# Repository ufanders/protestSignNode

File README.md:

# protestSignNode
This is a local driver for each of the protestSign display modules. It uses simplex RS-485 as the link back to the BeagleBone Black host and performs display refresh.

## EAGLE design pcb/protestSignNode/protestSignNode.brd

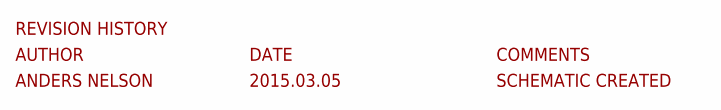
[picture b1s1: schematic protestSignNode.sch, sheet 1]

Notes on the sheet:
REVISION HISTORY
AUTHOR
DATE
COMMENTS
ANDERS NELSON
2015.03.05
SCHEMATIC CREATED

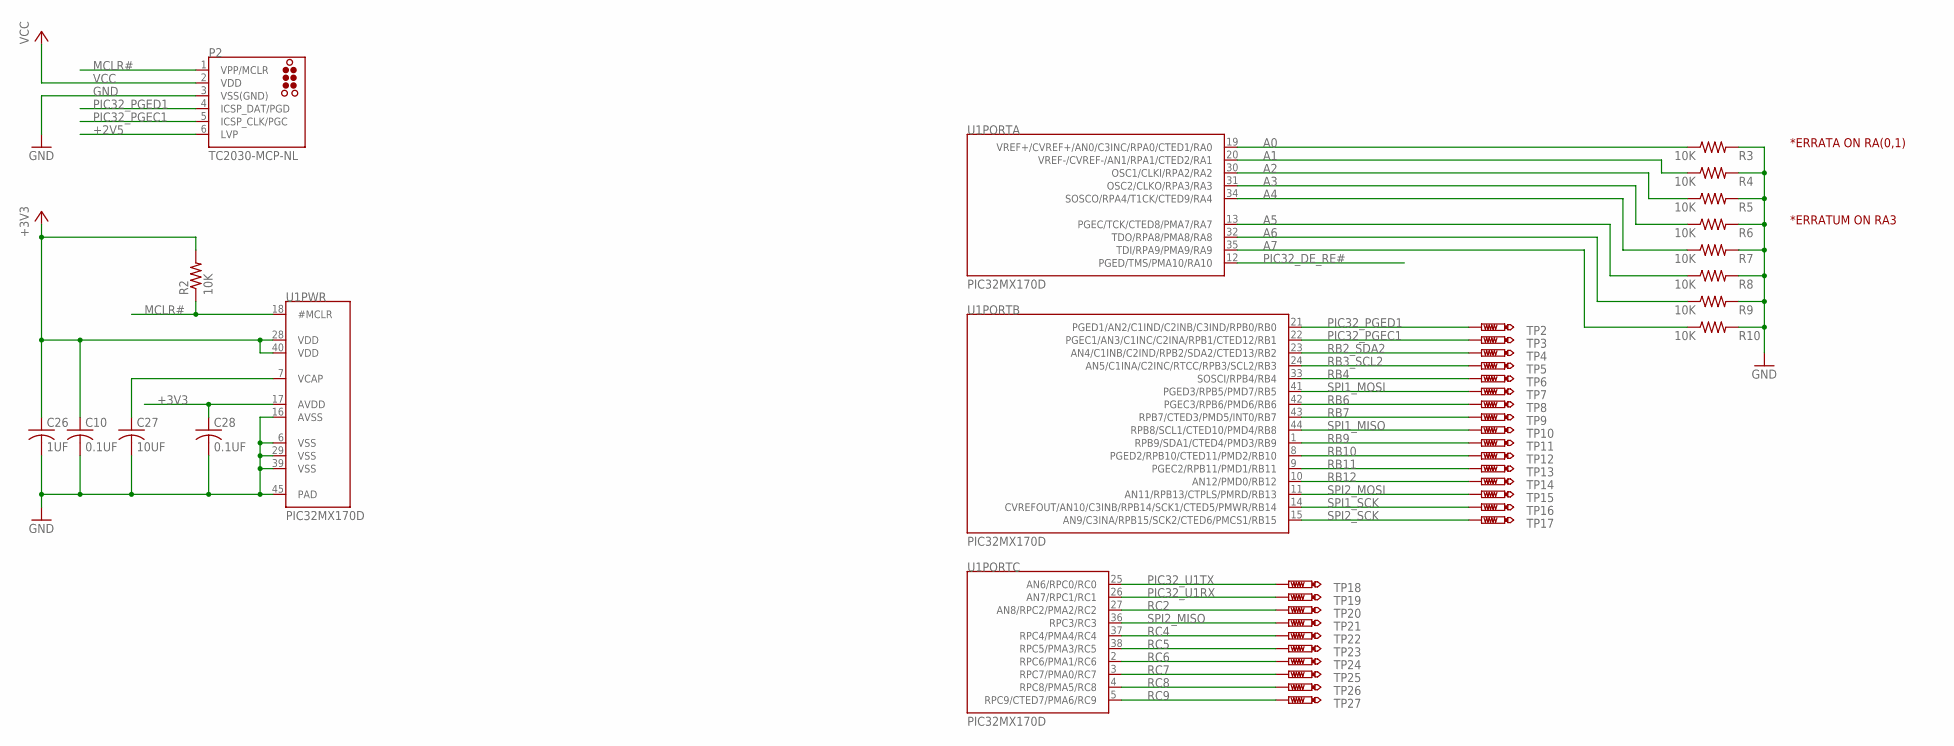
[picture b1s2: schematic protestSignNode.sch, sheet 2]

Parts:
C10, C28: 0.1UF; C0402
C26: 1UF; C0402
C27: 10UF; C0603
P2: TC2030-MCP-NL
R2, R3, R4, R5, R6, R7, R8, R9, R10: 10K; R0402
TP2, TP3, TP4, TP5, TP6, TP7, TP8, TP9, TP10, TP11, TP12, TP13, TP14, TP15, TP16, TP17, TP18, TP19, TP20, TP21, TP22, TP23, TP24, TP25, TP26, TP27: PTR1B1,27; B1,27
U1: PIC32MX170D; VTLA44

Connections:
+2V5: P2.6 (LVP)
+3V3: C10.1, C26.1, C28.1, R2.2, U1.17 (AVDD), U1.28 (VDD), U1.40 (VDD); also elsewhere on the board
A0: R3.1, U1.19 (VREF+/CVREF+/AN0/C3INC/RPA0/CTED1/RA0)
A1: R4.1, U1.20 (VREF-/CVREF-/AN1/RPA1/CTED2/RA1)
A2: R5.1, U1.30 (OSC1/CLKI/RPA2/RA2)
A3: R6.1, U1.31 (OSC2/CLKO/RPA3/RA3)
A4: R7.1, U1.34 (SOSCO/RPA4/T1CK/CTED9/RA4)
A5: R8.1, U1.13 (PGEC/TCK/CTED8/PMA7/RA7)
A6: R9.1, U1.32 (TDO/RPA8/PMA8/RA8)
A7: R10.1, U1.35 (TDI/RPA9/PMA9/RA9)
GND: C10.2, C26.2, C27.2, C28.2, P2.3 (VSS(GND)), R3.2, R4.2, R5.2, R6.2, R7.2, R8.2, R9.2, R10.2, U1.6 (VSS), U1.16 (AVSS), U1.29 (VSS), U1.39 (VSS), U1.45 (PAD); also elsewhere on the board
MCLR#: P2.1 (VPP/MCLR), R2.1, U1.18 (#MCLR)
unnamed: C27.1, U1.7 (VCAP)
PIC32_DE_RE#: U1.12 (PGED/TMS/PMA10/RA10); also elsewhere on the board
PIC32_PGEC1: P2.5 (ICSP_CLK/PGC), TP3.TP, U1.22 (PGEC1/AN3/C1INC/C2INA/RPB1/CTED12/RB1)
PIC32_PGED1: P2.4 (ICSP_DAT/PGD), TP2.TP, U1.21 (PGED1/AN2/C1IND/C2INB/C3IND/RPB0/RB0)
PIC32_U1RX: TP19.TP, U1.26 (AN7/RPC1/RC1); also elsewhere on the board
PIC32_U1TX: TP18.TP, U1.25 (AN6/RPC0/RC0); also elsewhere on the board
RB2_SDA2: TP4.TP, U1.23 (AN4/C1INB/C2IND/RPB2/SDA2/CTED13/RB2)
RB3_SCL2: TP5.TP, U1.24 (AN5/C1INA/C2INC/RTCC/RPB3/SCL2/RB3)
RB4: TP6.TP, U1.33 (SOSCI/RPB4/RB4)
RB6: TP8.TP, U1.42 (PGEC3/RPB6/PMD6/RB6)
RB7: TP9.TP, U1.43 (RPB7/CTED3/PMD5/INT0/RB7)
RB9: TP11.TP, U1.1 (RPB9/SDA1/CTED4/PMD3/RB9)
RB10: TP12.TP, U1.8 (PGED2/RPB10/CTED11/PMD2/RB10)
RB11: TP13.TP, U1.9 (PGEC2/RPB11/PMD1/RB11)
RB12: TP14.TP, U1.10 (AN12/PMD0/RB12)
RC2: TP20.TP, U1.27 (AN8/RPC2/PMA2/RC2)
RC4: TP22.TP, U1.37 (RPC4/PMA4/RC4)
RC5: TP23.TP, U1.38 (RPC5/PMA3/RC5)
RC6: TP24.TP, U1.2 (RPC6/PMA1/RC6)
RC7: TP25.TP, U1.3 (RPC7/PMA0/RC7)
RC8: TP26.TP, U1.4 (RPC8/PMA5/RC8)
RC9: TP27.TP, U1.5 (RPC9/CTED7/PMA6/RC9)
SPI1_MISO: TP10.TP, U1.44 (RPB8/SCL1/CTED10/PMD4/RB8)
SPI1_MOSI: TP7.TP, U1.41 (PGED3/RPB5/PMD7/RB5)
SPI1_SCK: TP16.TP, U1.14 (CVREFOUT/AN10/C3INB/RPB14/SCK1/CTED5/PM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)
SPI2_MISO: TP21.TP, U1.36 (RPC3/RC3)
SPI2_MOSI: TP15.TP, U1.11 (AN11/RPB13/CTPLS/PMRD/RB13)
SPI2_SCK: TP17.TP, U1.15 (AN9/C3INA/RPB15/SCK2/CTED6/PMCS1/RB15)
VCC: P2.2 (VDD)

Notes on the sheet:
*ERRATUM ON RA3
*ERRATA ON RA(0,1)

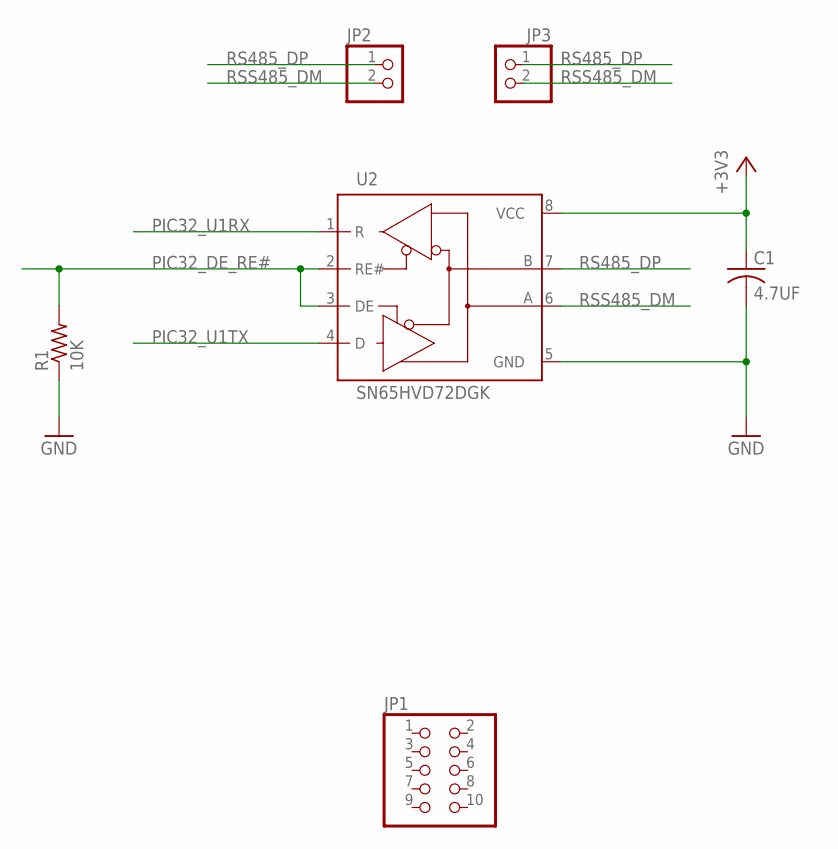
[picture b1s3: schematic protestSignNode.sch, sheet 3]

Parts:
C1: 4.7UF; C0603
JP1: PINHD-2X5; 2X05
JP2, JP3: PINHD-1X2/90; 1X02/90
R1: 10K; R0402
U2: SN65HVD72DGK; DGK

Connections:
+3V3: C1.1, U2.8 (VCC); also elsewhere on the board
GND: C1.2, R1.1, U2.5 (GND); also elsewhere on the board
PIC32_DE_RE#: R1.2, U2.2 (RE#), U2.3 (DE); also elsewhere on the board
PIC32_U1RX: U2.1 (R); also elsewhere on the board
PIC32_U1TX: U2.4 (D); also elsewhere on the board
RS485_DP: JP2.1, JP3.1, U2.7 (B)
RSS485_DM: JP2.2, JP3.2, U2.6 (A)

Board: 2 copper layers, 47 parts (1 on the bottom side), 41 nets, no tracks yet.

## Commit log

2015-03-09 Added framing. -Most stuff is there to start with.
2015-03-09 Added PCB files. -First commit.

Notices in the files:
parts and their libraries:
raveGearControl: ©2009 ROFA.cz
